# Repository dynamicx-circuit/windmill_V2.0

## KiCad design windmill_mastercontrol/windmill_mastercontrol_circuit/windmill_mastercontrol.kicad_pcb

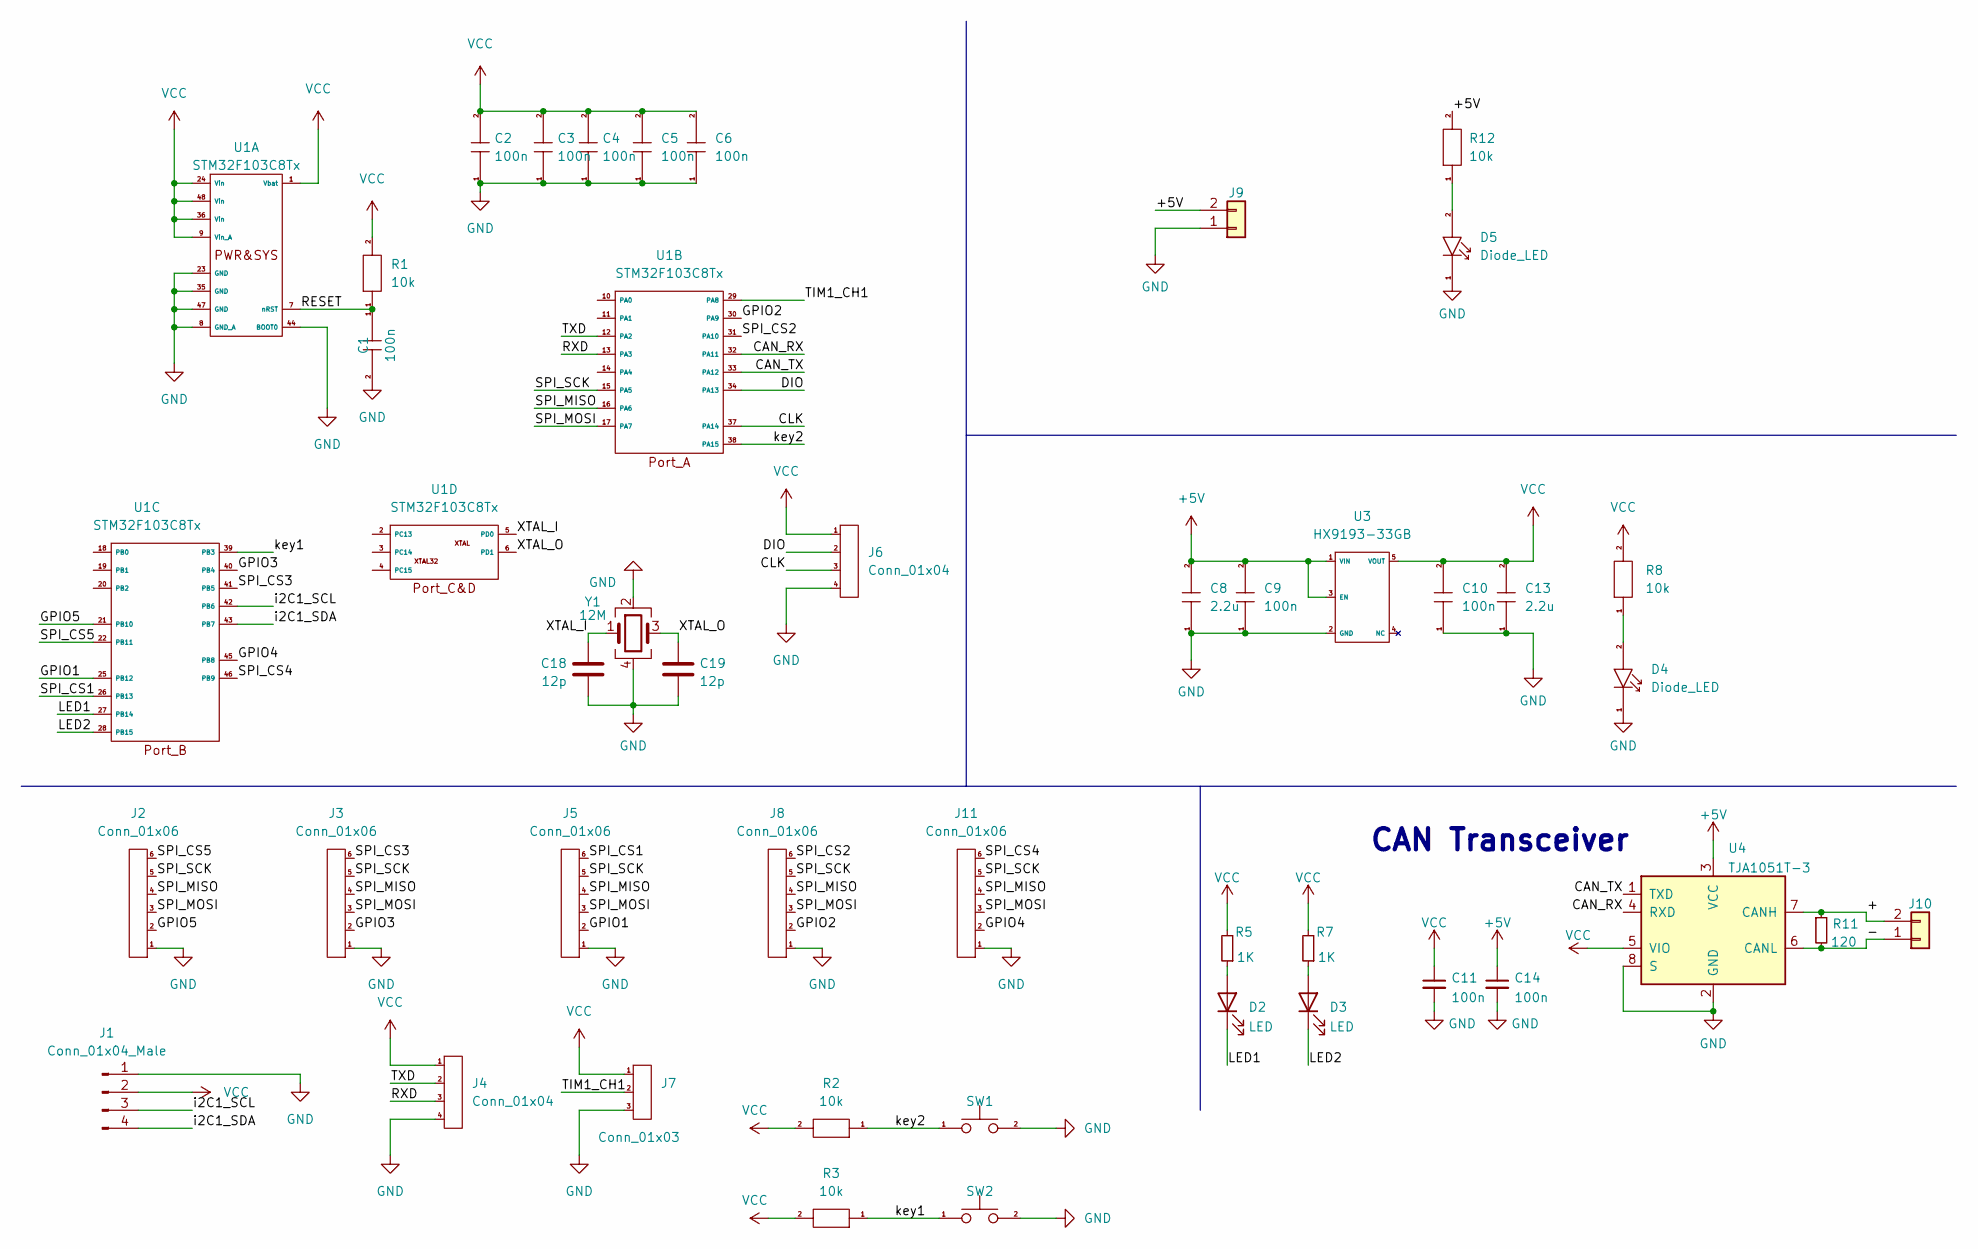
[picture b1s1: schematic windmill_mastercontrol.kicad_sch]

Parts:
C1, C2, C3, C4, C5, C6, C9, C10, C11, C14: 100n; C_0603_1608Metric
C8, C13: 2.2u; C_0603_1608Metric
C18, C19: 12p; C_0603_1608Metric_Pad1.08x0.95mm_HandSolder
D2, D3: LED; LED_0603_1608Metric
D4, D5: Diode_LED; LED_0603_1608Metric
J1: Conn_01x04_Male; PinSocket_1x04_P2.54mm_Vertical
J2, J3, J5, J8, J11: Conn_01x06; JST_GH_SM06B-GHS-TB_1x06-1MP_P1.25mm_Horizontal
J4, J6: Conn_01x04; GH1.25_V_4
J7: Conn_01x03; GH1.25_H_3
J9: Conn_01x02; AMASS_XT30PW-M_1x02_P2.50mm_Horizontal
J10: Conn_01x02; JST_GH_SM02B-GHS-TB_1x02-1MP_P1.25mm_Horizontal
R1, R2, R3, R8, R12: 10k; R_0603_1608Metric
R5, R7: 1K; R_0603_1608Metric
R11: 120; R_0603_1608Metric
SW1, SW2: SW_SPST_FSMSM
U1: STM32F103C8Tx; QFP-48_7070
U3: HX9193-33GB; TSOT-23-5_HandSoldering
U4: TJA1051T-3; SOIC-8_3.9x4.9mm_P1.27mm
Y1: 12M; Crystal_SMD_3225-4Pin_3.2x2.5mm

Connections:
+5V: C8.2, C9.2, C14.1, J9.2, R12.2, U3.1 (VIN), U3.3 (EN), U4.3 (VCC)
/+: J10.2, R11.1, U4.7 (CANH)
/-: J10.1, R11.2, U4.6 (CANL)
/CAN_RX: U1.32 (PA11), U4.4 (RXD)
/CAN_TX: U1.33 (PA12), U4.1 (TXD)
/CLK: J6.3, U1.37 (PA14)
/DIO: J6.2, U1.34 (PA13)
/GPIO1: J5.2, U1.25 (PB12)
/GPIO2: J8.2, U1.30 (PA9)
/GPIO3: J3.2, U1.40 (PB4)
/GPIO4: J11.2, U1.45 (PB8)
/GPIO5: J2.2, U1.21 (PB10)
/LED1: D2.1 (K), U1.27 (PB14)
/LED2: D3.1 (K), U1.28 (PB15)
/RESET: C1.1, R1.1, U1.7 (nRST)
/RXD: J4.3, U1.13 (PA3)
/SPI_CS1: J5.6, U1.26 (PB13)
/SPI_CS2: J8.6, U1.31 (PA10)
/SPI_CS3: J3.6, U1.41 (PB5)
/SPI_CS4: J11.6, U1.46 (PB9)
/SPI_CS5: J2.6, U1.22 (PB11)
/SPI_MISO: J2.4, J3.4, J5.4, J8.4, J11.4, U1.16 (PA6)
/SPI_MOSI: J2.3, J3.3, J5.3, J8.3, J11.3, U1.17 (PA7)
/SPI_SCK: J2.5, J3.5, J5.5, J8.5, J11.5, U1.15 (PA5)
/TIM1_CH1: J7.2, U1.29 (PA8)
/TXD: J4.2, U1.12 (PA2)
/XTAL_I: C18.2, U1.5 (PD0), Y1.1
/XTAL_O: C19.2, U1.6 (PD1), Y1.3
/i2C1_SCL: J1.3, U1.42 (PB6)
/i2C1_SDA: J1.4, U1.43 (PB7)
/key1: R3.1, SW2.1, U1.39 (PB3)
/key2: R2.1, SW1.1, U1.38 (PA15)
GND: C1.2, C2.1, C3.1, C4.1, C5.1, C6.1, C8.1, C9.1, C10.1, C11.2, C13.1, C14.2, C18.1, C19.1, D4.1 (Cathode), D5.1 (Cathode), J1.1, J2.1, J3.1, J4.4, J5.1, J6.4, J7.3, J8.1, J9.1, J11.1, SW1.2, SW2.2, U1.8 (GND_A), U1.23 (GND), U1.35 (GND), U1.44 (BOOT0), U1.47 (GND), U3.2 (GND), U4.2 (GND), U4.8 (S), Y1.2, Y1.4
unnamed: D2.2 (A), R5.1
unnamed: D3.2 (A), R7.1
unnamed: D4.2 (Anode), R8.1
unnamed: D5.2 (Anode), R12.1
VCC: C2.2, C3.2, C4.2, C5.2, C6.2, C10.2, C11.1, C13.2, J1.2, J4.1, J6.1, J7.1, R1.2, R2.2, R3.2, R5.2, R7.2, R8.2, U1.1 (Vbat), U1.9 (Vin_A), U1.24 (Vin), U1.36 (Vin), U1.48 (Vin), U3.5 (VOUT), U4.5 (VIO)

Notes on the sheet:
CAN Transceiver

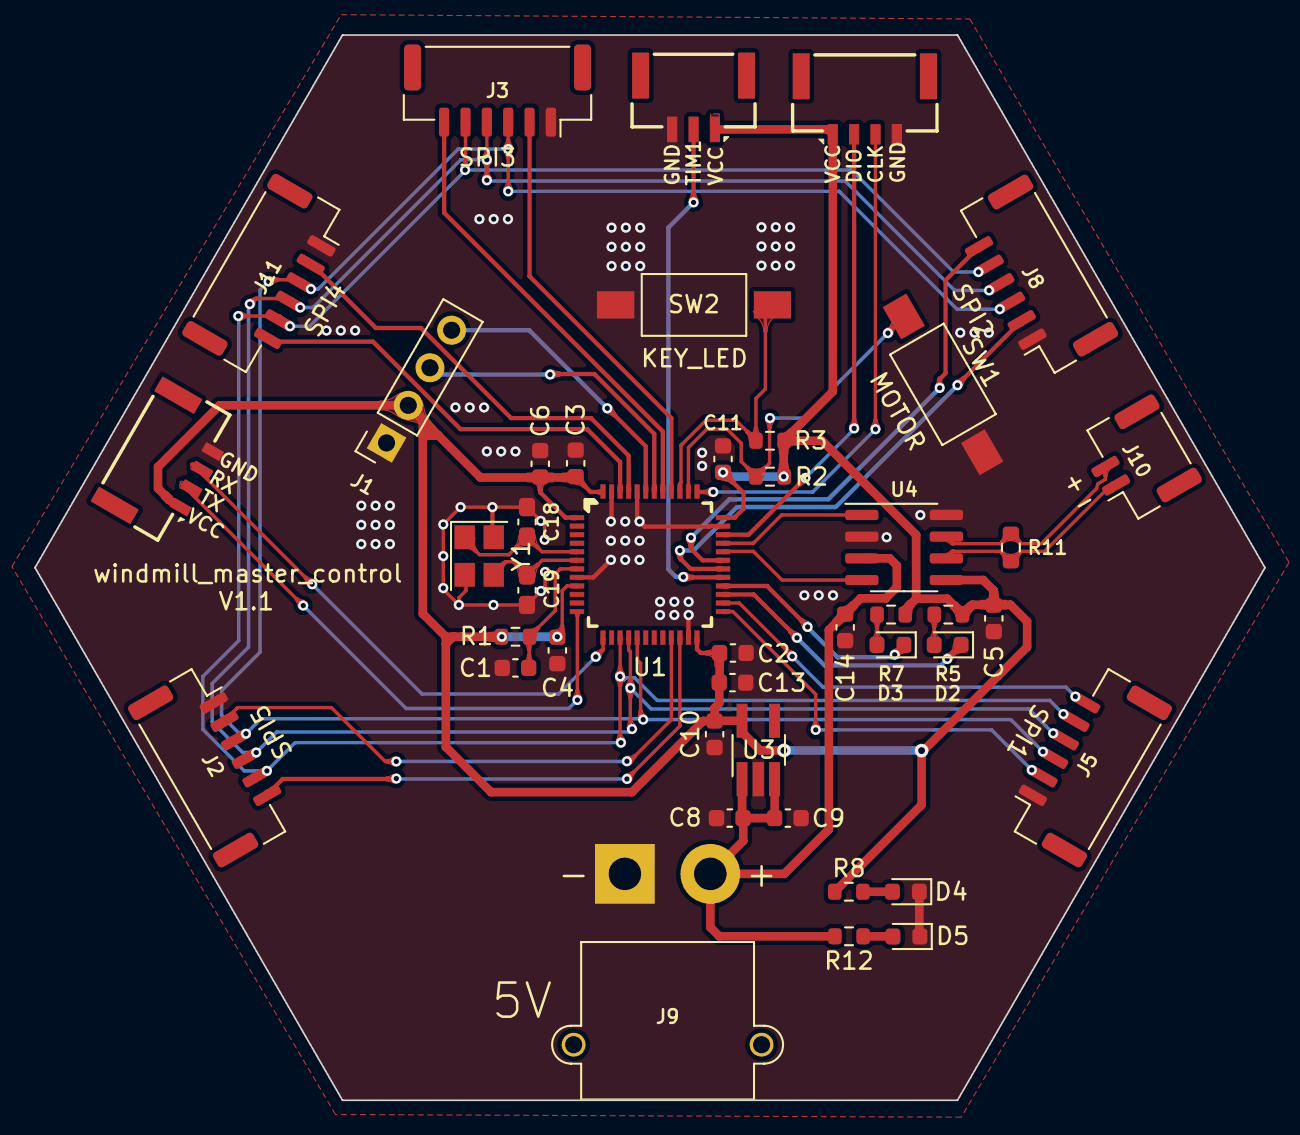
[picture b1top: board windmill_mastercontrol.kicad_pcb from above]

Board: 2 copper layers, 72.0 x 62.4 mm, 40 parts (0 on the bottom side), 33 nets.

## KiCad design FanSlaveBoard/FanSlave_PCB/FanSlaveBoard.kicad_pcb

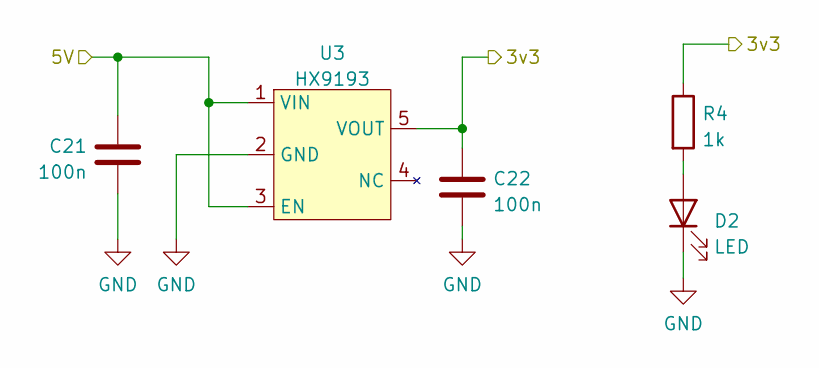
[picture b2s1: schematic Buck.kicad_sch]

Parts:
C21, C22: 100n; C_0603_1608Metric_Pad1.08x0.95mm_HandSolder
D2: LED; LED_0603_1608Metric
R4: 1k; R_0603_1608Metric_Pad0.98x0.95mm_HandSolder
U3: HX9193; SOT-23-5_HandSoldering

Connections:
/MCU/3v3: C22.2, R4.1, U3.5 (VOUT); also elsewhere on the board
/PWR/5V: C21.2, U3.1 (VIN), U3.3 (EN); also elsewhere on the board
GND: C21.1, C22.1, D2.1 (K), U3.2 (GND); also elsewhere on the board
unnamed: D2.2 (A), R4.2

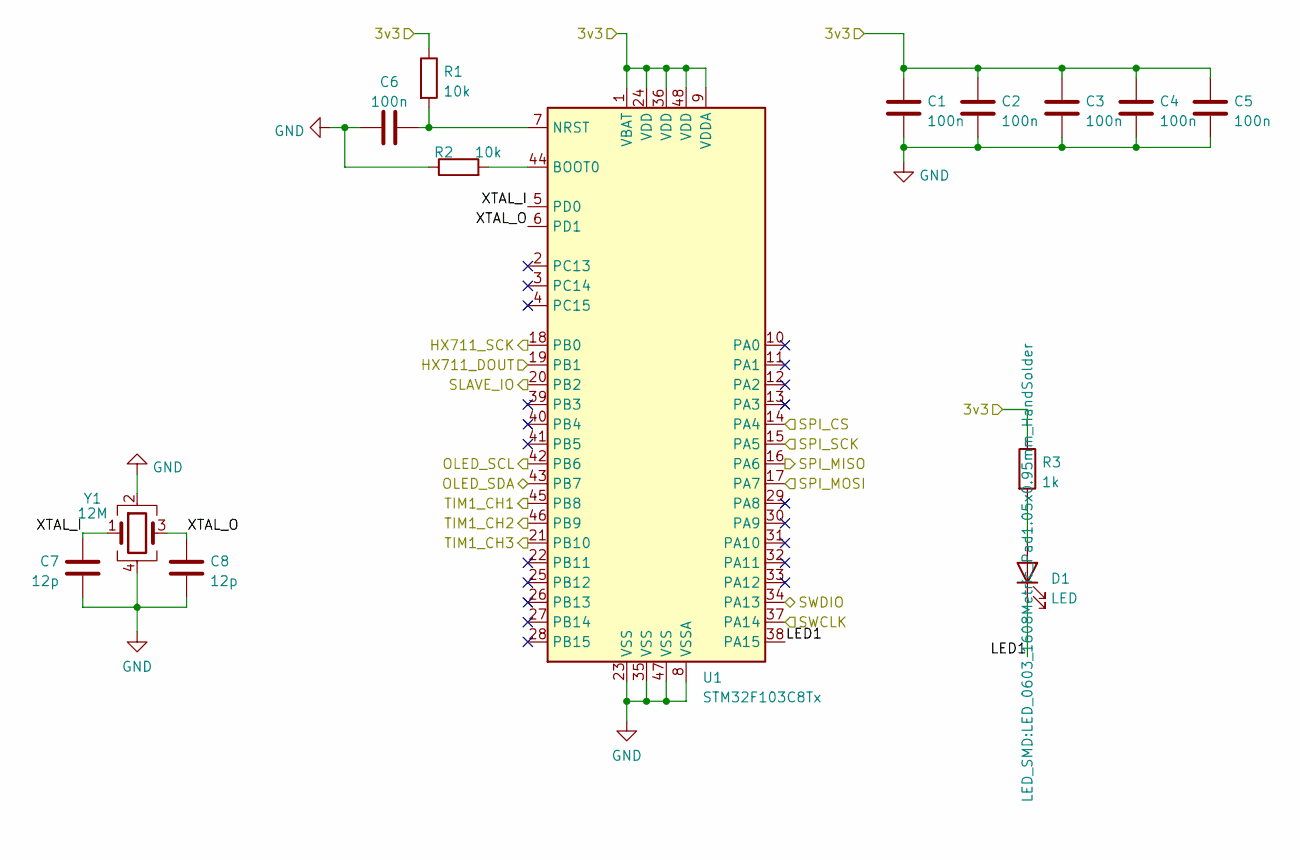
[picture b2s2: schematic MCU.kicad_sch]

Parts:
C1, C2, C3, C4, C5, C6: 100n; C_0603_1608Metric_Pad1.08x0.95mm_HandSolder
C7, C8: 12p; C_0603_1608Metric_Pad1.08x0.95mm_HandSolder
D1: LED; LED_0603_1608Metric_Pad1.05x0.95mm_HandSolder
R1, R2: 10k; R_0603_1608Metric_Pad0.98x0.95mm_HandSolder
R3: 1k; R_0603_1608Metric_Pad0.98x0.95mm_HandSolder
U1: STM32F103C8Tx; LQFP-48_7x7mm_P0.5mm
Y1: 12M; Crystal_SMD_3225-4Pin_3.2x2.5mm_HandSoldering

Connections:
/MCU/3v3: C1.1, C2.1, C3.1, C4.1, C5.1, R1.1, R3.1, U1.1 (VBAT), U1.9 (VDDA), U1.24 (VDD), U1.36 (VDD), U1.48 (VDD); also elsewhere on the board
/MCU/HX711_DOUT: U1.19 (PB1); also elsewhere on the board
/MCU/HX711_SCK: U1.18 (PB0); also elsewhere on the board
/MCU/LED1: D1.1 (K), U1.38 (PA15)
/MCU/OLED_SCL: U1.42 (PB6); also elsewhere on the board
/MCU/OLED_SDA: U1.43 (PB7); also elsewhere on the board
/MCU/SLAVE_IO: U1.20 (PB2); also elsewhere on the board
/MCU/SPI_CS: U1.14 (PA4); also elsewhere on the board
/MCU/SPI_MISO: U1.16 (PA6); also elsewhere on the board
/MCU/SPI_MOSI: U1.17 (PA7); also elsewhere on the board
/MCU/SPI_SCK: U1.15 (PA5); also elsewhere on the board
/MCU/SWCLK: U1.37 (PA14); also elsewhere on the board
/MCU/SWDIO: U1.34 (PA13); also elsewhere on the board
/MCU/TIM1_CH1: U1.45 (PB8); also elsewhere on the board
/MCU/TIM1_CH2: U1.46 (PB9); also elsewhere on the board
/MCU/TIM1_CH3: U1.21 (PB10); also elsewhere on the board
/MCU/XTAL_I: C7.2, U1.5 (PD0), Y1.1
/MCU/XTAL_O: C8.2, U1.6 (PD1), Y1.3
GND: C1.2, C2.2, C3.2, C4.2, C5.2, C6.1, C7.1, C8.1, R2.1, U1.8 (VSSA), U1.23 (VSS), U1.35 (VSS), U1.47 (VSS), Y1.2, Y1.4; also elsewhere on the board
unnamed: C6.2, R1.2, U1.7 (NRST)
unnamed: D1.2 (A), R3.2
unnamed: R2.2, U1.44 (BOOT0)

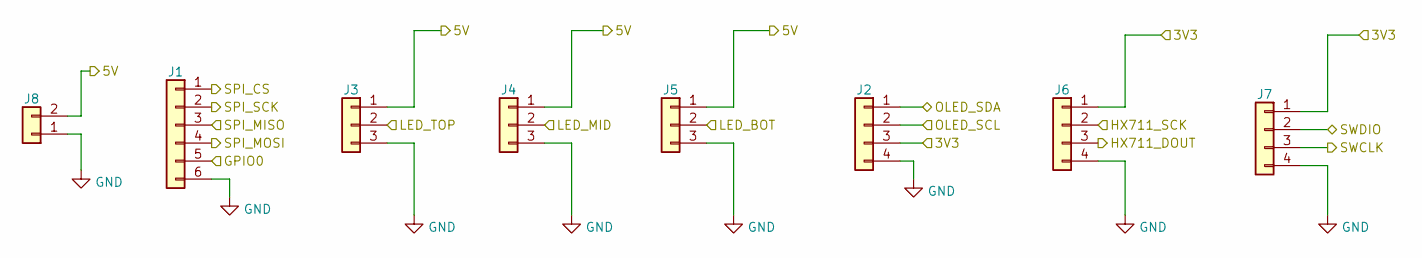
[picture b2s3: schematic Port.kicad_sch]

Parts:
J1: Conn_01x06; JST_GH_SM06B-GHS-TB_1x06-1MP_P1.25mm_Horizontal
J2, J6: Conn_01x04; PinHeader_1x04_P2.54mm_Vertical
J3, J4, J5: Conn_01x03; PinHeader_1x03_P2.54mm_Vertical
J7: Conn_01x04; JST_GH_SM04B-GHS-TB_1x04-1MP_P1.25mm_Horizontal
J8: Conn_01x02; AMASS_XT30PW-M_1x02_P2.50mm_Horizontal

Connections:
/MCU/3v3: J2.3, J6.1, J7.1; also elsewhere on the board
/MCU/HX711_DOUT: J6.3; also elsewhere on the board
/MCU/HX711_SCK: J6.2; also elsewhere on the board
/MCU/OLED_SCL: J2.2; also elsewhere on the board
/MCU/OLED_SDA: J2.1; also elsewhere on the board
/MCU/SLAVE_IO: J1.5; also elsewhere on the board
/MCU/SPI_CS: J1.1; also elsewhere on the board
/MCU/SPI_MISO: J1.3; also elsewhere on the board
/MCU/SPI_MOSI: J1.4; also elsewhere on the board
/MCU/SPI_SCK: J1.2; also elsewhere on the board
/MCU/SWCLK: J7.3; also elsewhere on the board
/MCU/SWDIO: J7.2; also elsewhere on the board
/MCU/TIM1_CH1: J3.2; also elsewhere on the board
/MCU/TIM1_CH2: J4.2; also elsewhere on the board
/MCU/TIM1_CH3: J5.2; also elsewhere on the board
/PWR/5V: J3.1, J4.1, J5.1, J8.2; also elsewhere on the board
GND: J1.6, J2.4, J3.3, J4.3, J5.3, J6.4, J7.4, J8.1; also elsewhere on the board

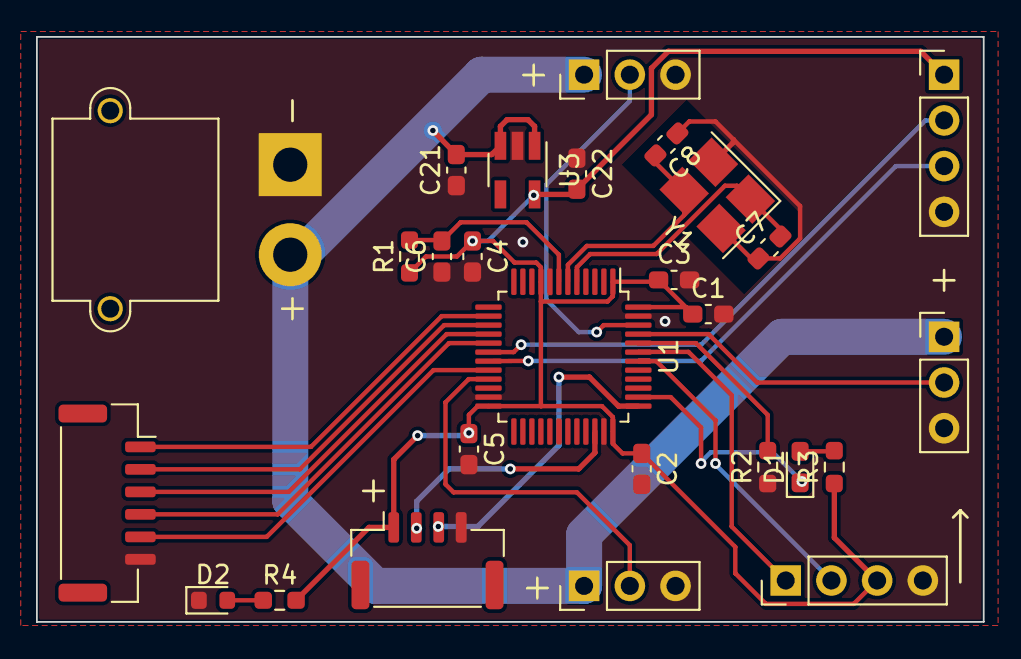
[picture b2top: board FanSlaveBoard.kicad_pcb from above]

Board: 2 copper layers, 52.6 x 32.5 mm, 27 parts (0 on the bottom side), 24 nets.

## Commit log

2023-04-14 The first commit
